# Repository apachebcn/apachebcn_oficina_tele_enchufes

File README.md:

# apachebcn_oficina_tele_enchufes

Control remoto de enchufes, pensado para la oficina para encender y apagar fácilmente todos los dispositivos.
Incluye proyecto de Kicad para fabricar las placas.

El proyecto consta de 2 placas pcbs.
1 pcb para conectar el arduino a los relés. (yo lo tengo debajo de la mesa, porque no es necesario tener acceso nivisibilidad a esta placa)
1 pcb de interfaz donde están los pulsadores para activar/desactivar los relés, y leds de testigos para saber que relés están encendidos.

Foto de pcb de la interfaz:

Foto de pcb de los relés:

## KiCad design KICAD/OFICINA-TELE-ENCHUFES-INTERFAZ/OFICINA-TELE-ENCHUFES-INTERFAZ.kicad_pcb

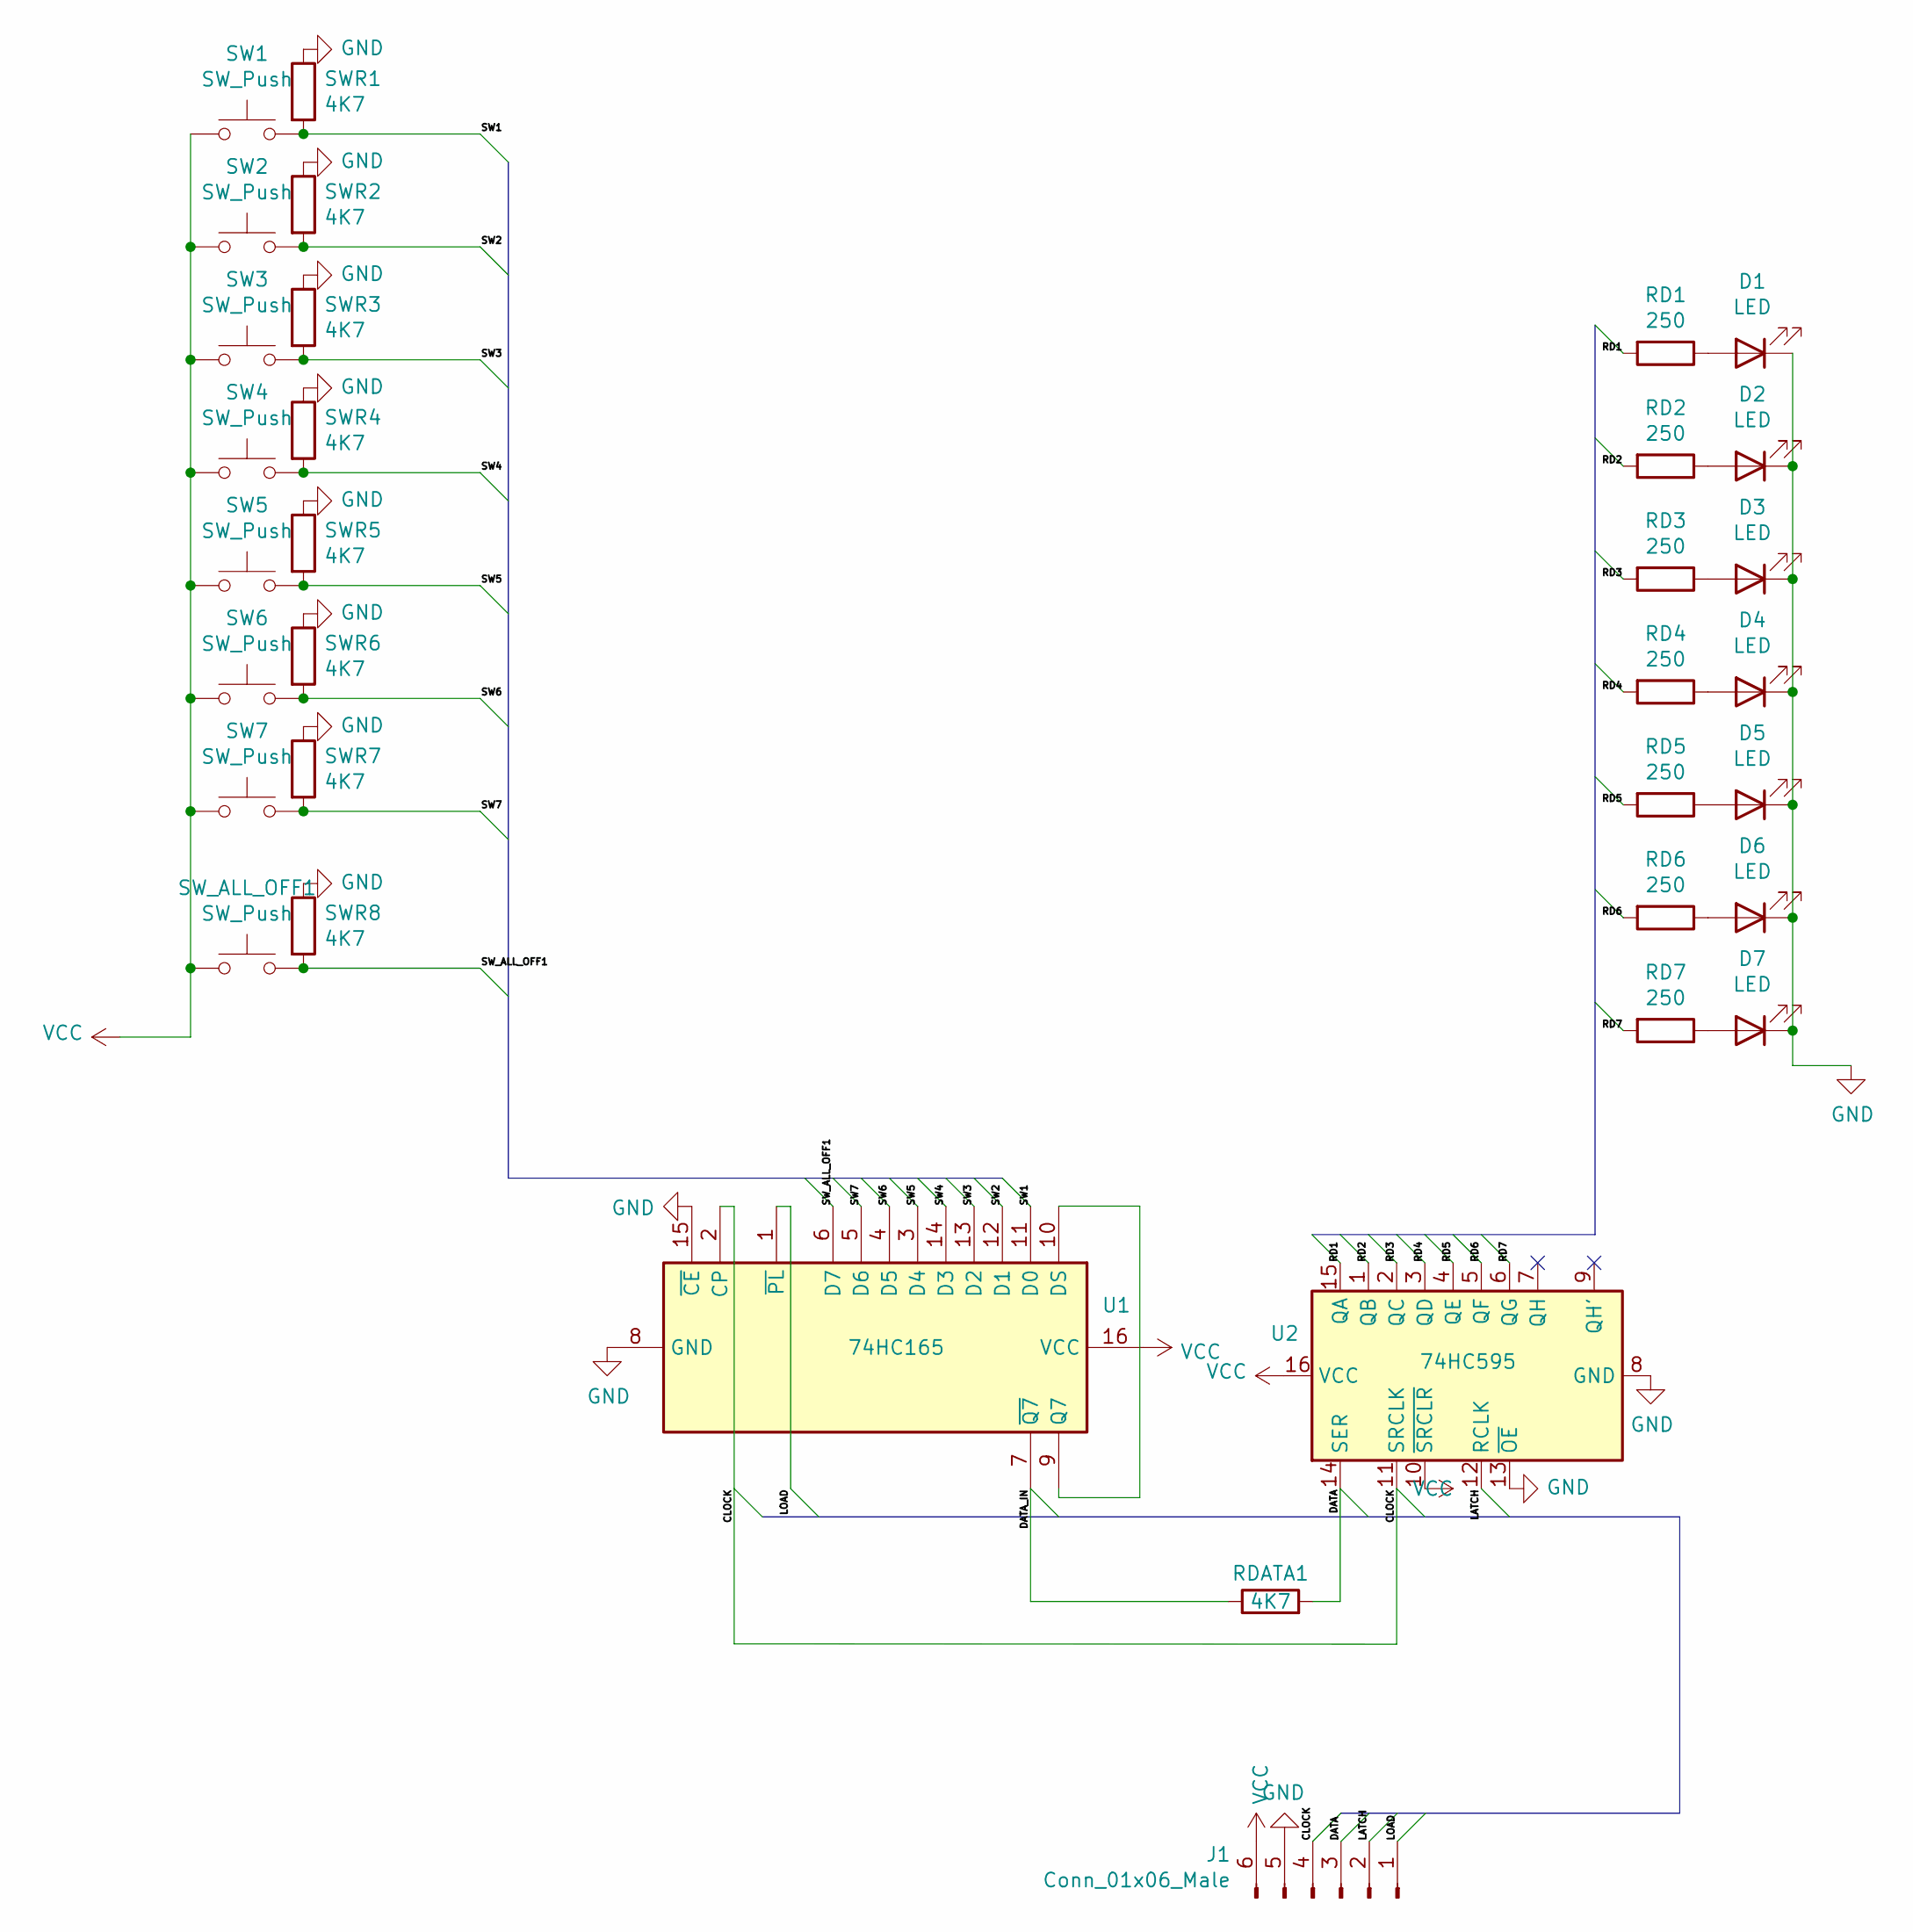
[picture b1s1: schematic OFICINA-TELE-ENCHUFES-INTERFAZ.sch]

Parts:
D1, D2, D3, D4, D5, D6, D7: LED; D_1206_3216Metric
J1: Conn_01x06_Male; JST_EH_B6B-EH-A_1x06_P2.50mm_Vertical
RD1, RD2, RD3, RD4, RD5, RD6, RD7: 250; R_1206_3216Metric
RDATA1: 4K7; R_1206_3216Metric
SW1, SW2, SW3, SW4, SW5, SW6, SW7: SW_Push; SW_PUSH-12mm
SWR1, SWR2, SWR3, SWR4, SWR5, SWR6, SWR7, SWR8: 4K7; R_1206_3216Metric
SW_ALL_OFF1: SW_Push; SW_PUSH-12mm
U1: 74HC165; DIP-16_W7.62mm
U2: 74HC595; DIP-16_W7.62mm

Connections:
/CLOCK: J1.4, U1.2 (CP), U2.11 (SRCLK)
/DATA: J1.3, RDATA1.2, U2.14 (SER)
/DATA_IN: RDATA1.1, U1.7 (~Q7)
/LATCH: J1.2, U2.12 (RCLK)
/LOAD: J1.1, U1.1 (~PL)
/RD1: RD1.2, U2.15 (QA)
/RD2: RD2.2, U2.1 (QB)
/RD3: RD3.2, U2.2 (QC)
/RD4: RD4.2, U2.3 (QD)
/RD5: RD5.2, U2.4 (QE)
/RD6: RD6.2, U2.5 (QF)
/RD7: RD7.2, U2.6 (QG)
/SW1: SW1.2, SWR1.2, U1.11 (D0)
/SW2: SW2.2, SWR2.2, U1.12 (D1)
/SW3: SW3.2, SWR3.2, U1.13 (D2)
/SW4: SW4.2, SWR4.2, U1.14 (D3)
/SW5: SW5.2, SWR5.2, U1.3 (D4)
/SW6: SW6.2, SWR6.2, U1.4 (D5)
/SW7: SW7.2, SWR7.2, U1.5 (D6)
/SW_ALL_OFF1: SWR8.2, SW_ALL_OFF1.2, U1.6 (D7)
GND: D1.1 (K), D2.1 (K), D3.1 (K), D4.1 (K), D5.1 (K), D6.1 (K), D7.1 (K), J1.5, SWR1.1, SWR2.1, SWR3.1, SWR4.1, SWR5.1, SWR6.1, SWR7.1, SWR8.1, U1.8 (GND), U1.15 (~CE), U2.8 (GND), U2.13 (~OE)
unnamed: D1.2 (A), RD1.1
unnamed: D2.2 (A), RD2.1
unnamed: D3.2 (A), RD3.1
unnamed: D4.2 (A), RD4.1
unnamed: D5.2 (A), RD5.1
unnamed: D6.2 (A), RD6.1
unnamed: D7.2 (A), RD7.1
unnamed: U1.9 (Q7), U1.10 (DS)
VCC: J1.6, SW1.1, SW2.1, SW3.1, SW4.1, SW5.1, SW6.1, SW7.1, SW_ALL_OFF1.1, U1.16 (VCC), U2.10 (~SRCLR), U2.16 (VCC)

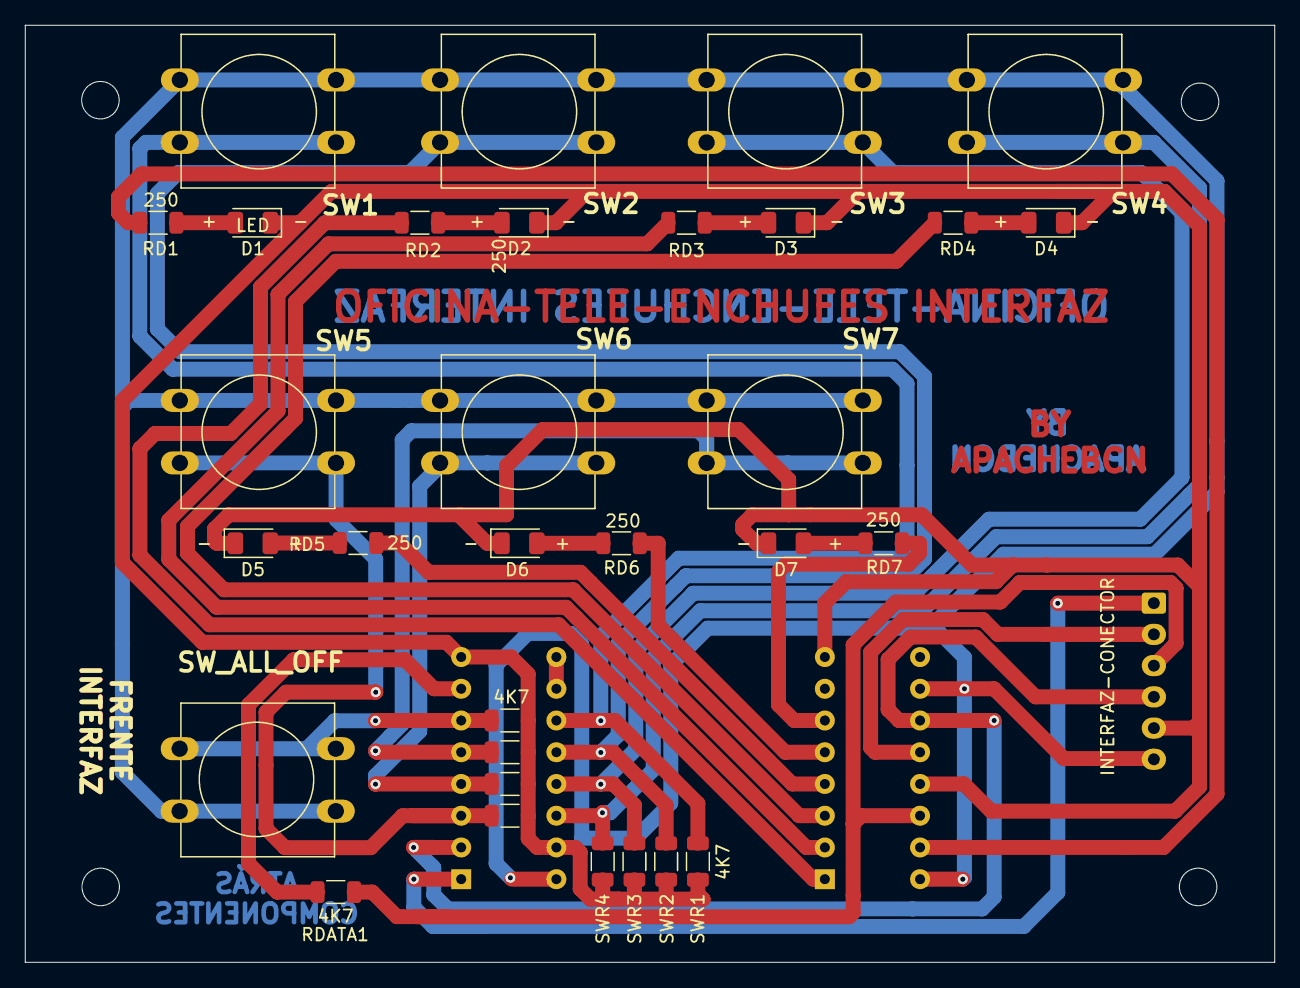
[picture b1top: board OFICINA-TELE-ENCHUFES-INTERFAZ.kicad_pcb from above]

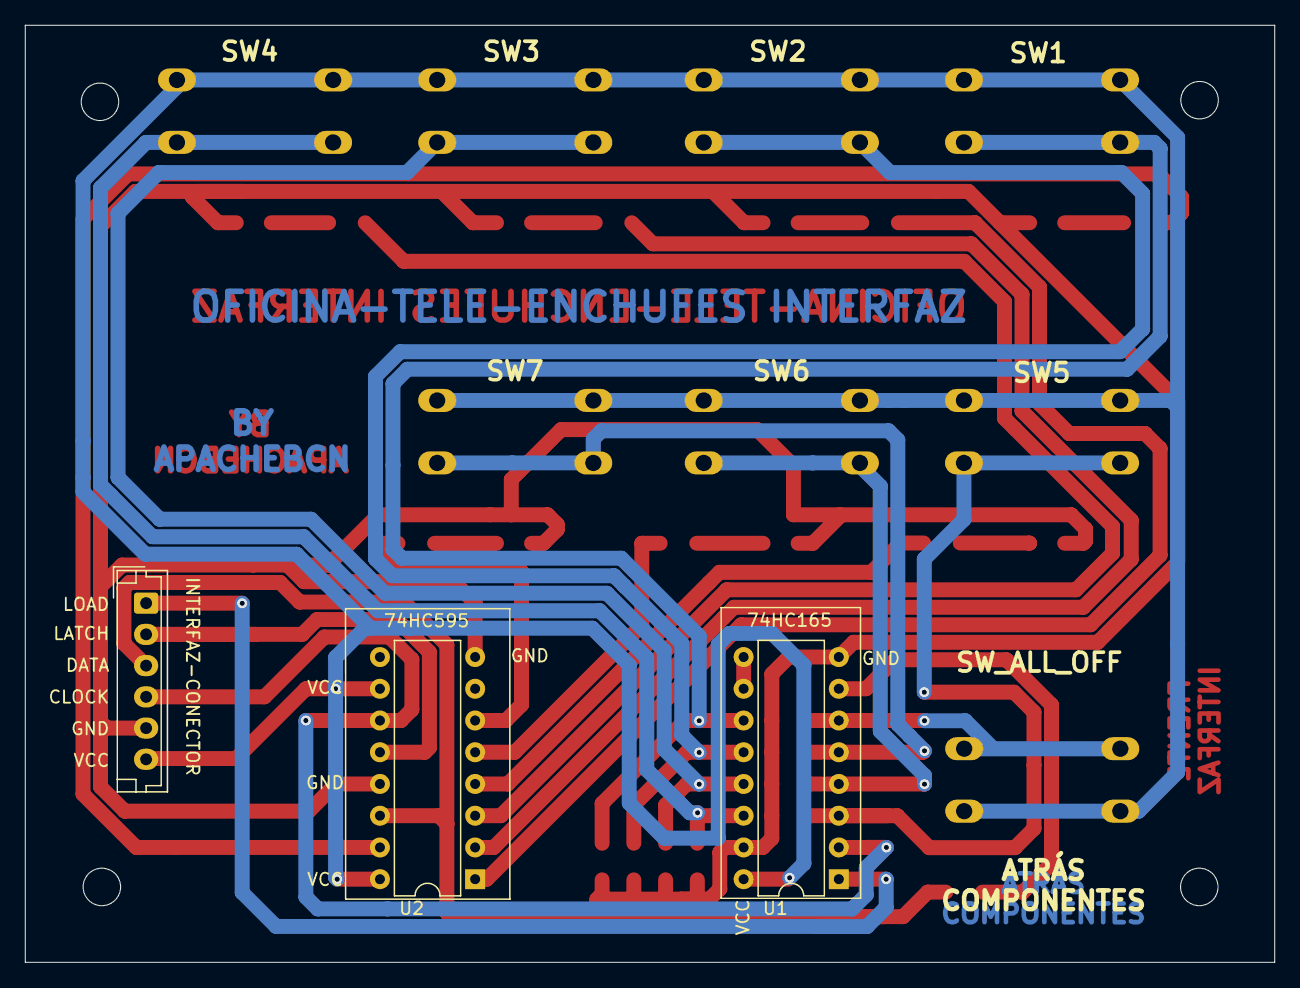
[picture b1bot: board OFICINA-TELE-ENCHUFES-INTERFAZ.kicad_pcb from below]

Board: 2 copper layers, 100.0 x 75.0 mm, 34 parts (3 on the bottom side), 30 nets.

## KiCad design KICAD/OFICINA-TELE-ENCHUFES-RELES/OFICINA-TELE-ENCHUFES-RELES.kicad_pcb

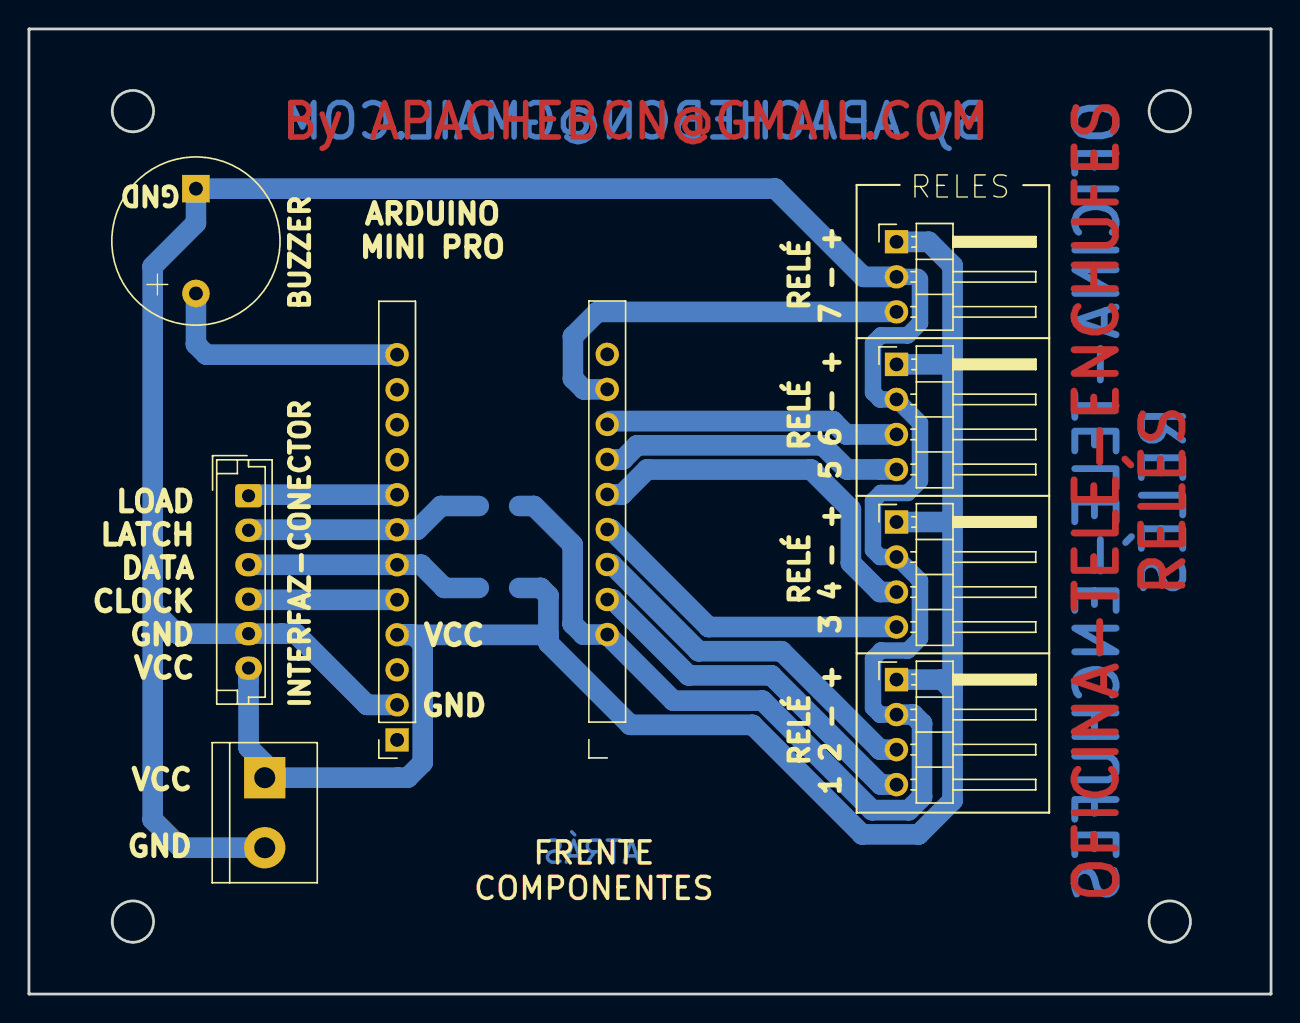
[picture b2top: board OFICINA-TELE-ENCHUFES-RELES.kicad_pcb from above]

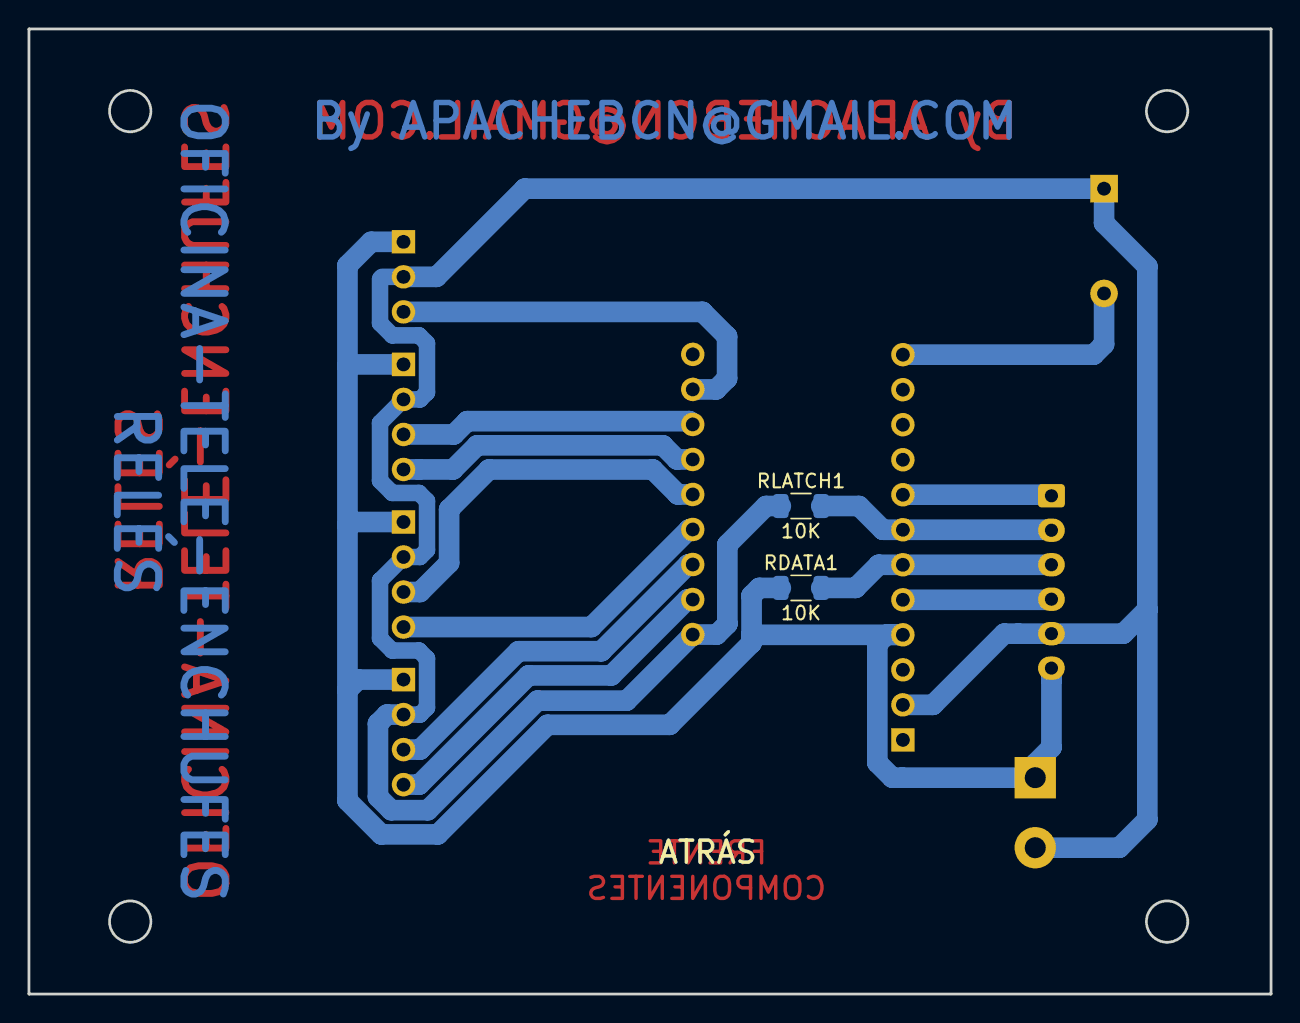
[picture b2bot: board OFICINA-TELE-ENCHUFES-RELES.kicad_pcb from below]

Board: 2 copper layers, 90.1 x 70.0 mm, 11 parts (2 on the bottom side), 14 nets.

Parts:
ARDUINO_L1: ARDUINO L; PinSocket_1x13_P2.54mm_Vertical
ARDUINO_R1: ARDUINO_R; PinSocket_1x13_P2.54mm_Vertical
BUZZER1: SPEAKER; Buzzer_12x9.5RM7.6
INTERFAZ-CONECTOR1: + - CLOCK DATA LATCH LOAD; JST_EH_B6B-EH-A_1x06_P2.50mm_Vertical
J1: Screw_Terminal_01x02; TerminalBlock_bornier-2_P5.08mm
RDATA1: 10K; R_1206_3216Metric
RELE-1-2: + - 1 2; PinHeader_1x04_P2.54mm_Horizontal
RELE-3-4, RELE-5-6: + - 3 4; PinHeader_1x04_P2.54mm_Horizontal
RELE-7: + - 3 4; PinHeader_1x03_P2.54mm_Horizontal
RLATCH1: 10K; R_1206_3216Metric

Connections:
/12: ARDUINO_R1.12, BUZZER1.2
/CLOCK: ARDUINO_R1.5, INTERFAZ-CONECTOR1.4
/DATA: ARDUINO_R1.6, INTERFAZ-CONECTOR1.3, RDATA1.2
/LATCH: ARDUINO_R1.7, INTERFAZ-CONECTOR1.2, RLATCH1.2
/LOAD: ARDUINO_R1.8, INTERFAZ-CONECTOR1.1
/RELE1: ARDUINO_L1.5, RELE-1-2.4
/RELE2: ARDUINO_L1.6, RELE-1-2.3
/RELE3: ARDUINO_L1.7, RELE-3-4.4
/RELE4: ARDUINO_L1.8, RELE-3-4.3
/RELE5: ARDUINO_L1.9, RELE-5-6.4
/RELE6: ARDUINO_L1.10, RELE-5-6.3
/RELE7: ARDUINO_L1.11, RELE-7.3
GND: ARDUINO_L1.4, ARDUINO_R1.2, BUZZER1.1, INTERFAZ-CONECTOR1.5, J1.2, RELE-1-2.2, RELE-3-4.2, RELE-5-6.2, RELE-7.2, RLATCH1.1
VCC: ARDUINO_R1.4, INTERFAZ-CONECTOR1.6, J1.1, RDATA1.1, RELE-1-2.1, RELE-3-4.1, RELE-5-6.1, RELE-7.1

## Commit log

2024-09-08 readme
